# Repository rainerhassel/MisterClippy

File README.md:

# MisterClippy

> Clipping Detector Module

## Dependencies

This project uses symbols from the [moPsy-KiCad-resources](https://github.com/moPsy-project/moPsy-KiCad-resources).

## License

This work is licensed under a [Creative Commons Attribution-ShareAlike 4.0 International License](http://creativecommons.org/licenses/by-sa/4.0/).

BY: Patrick Pickel (@rainerhassel) and Stefan Haun (@penguineer)

See [LICENSE.txt](LICENSE.txt) for details.

Using [moPsy-KiCad-resources](https://github.com/moPsy-project/moPsy-KiCad-resources) by Stefan Haun (mail@tuxathome.de).

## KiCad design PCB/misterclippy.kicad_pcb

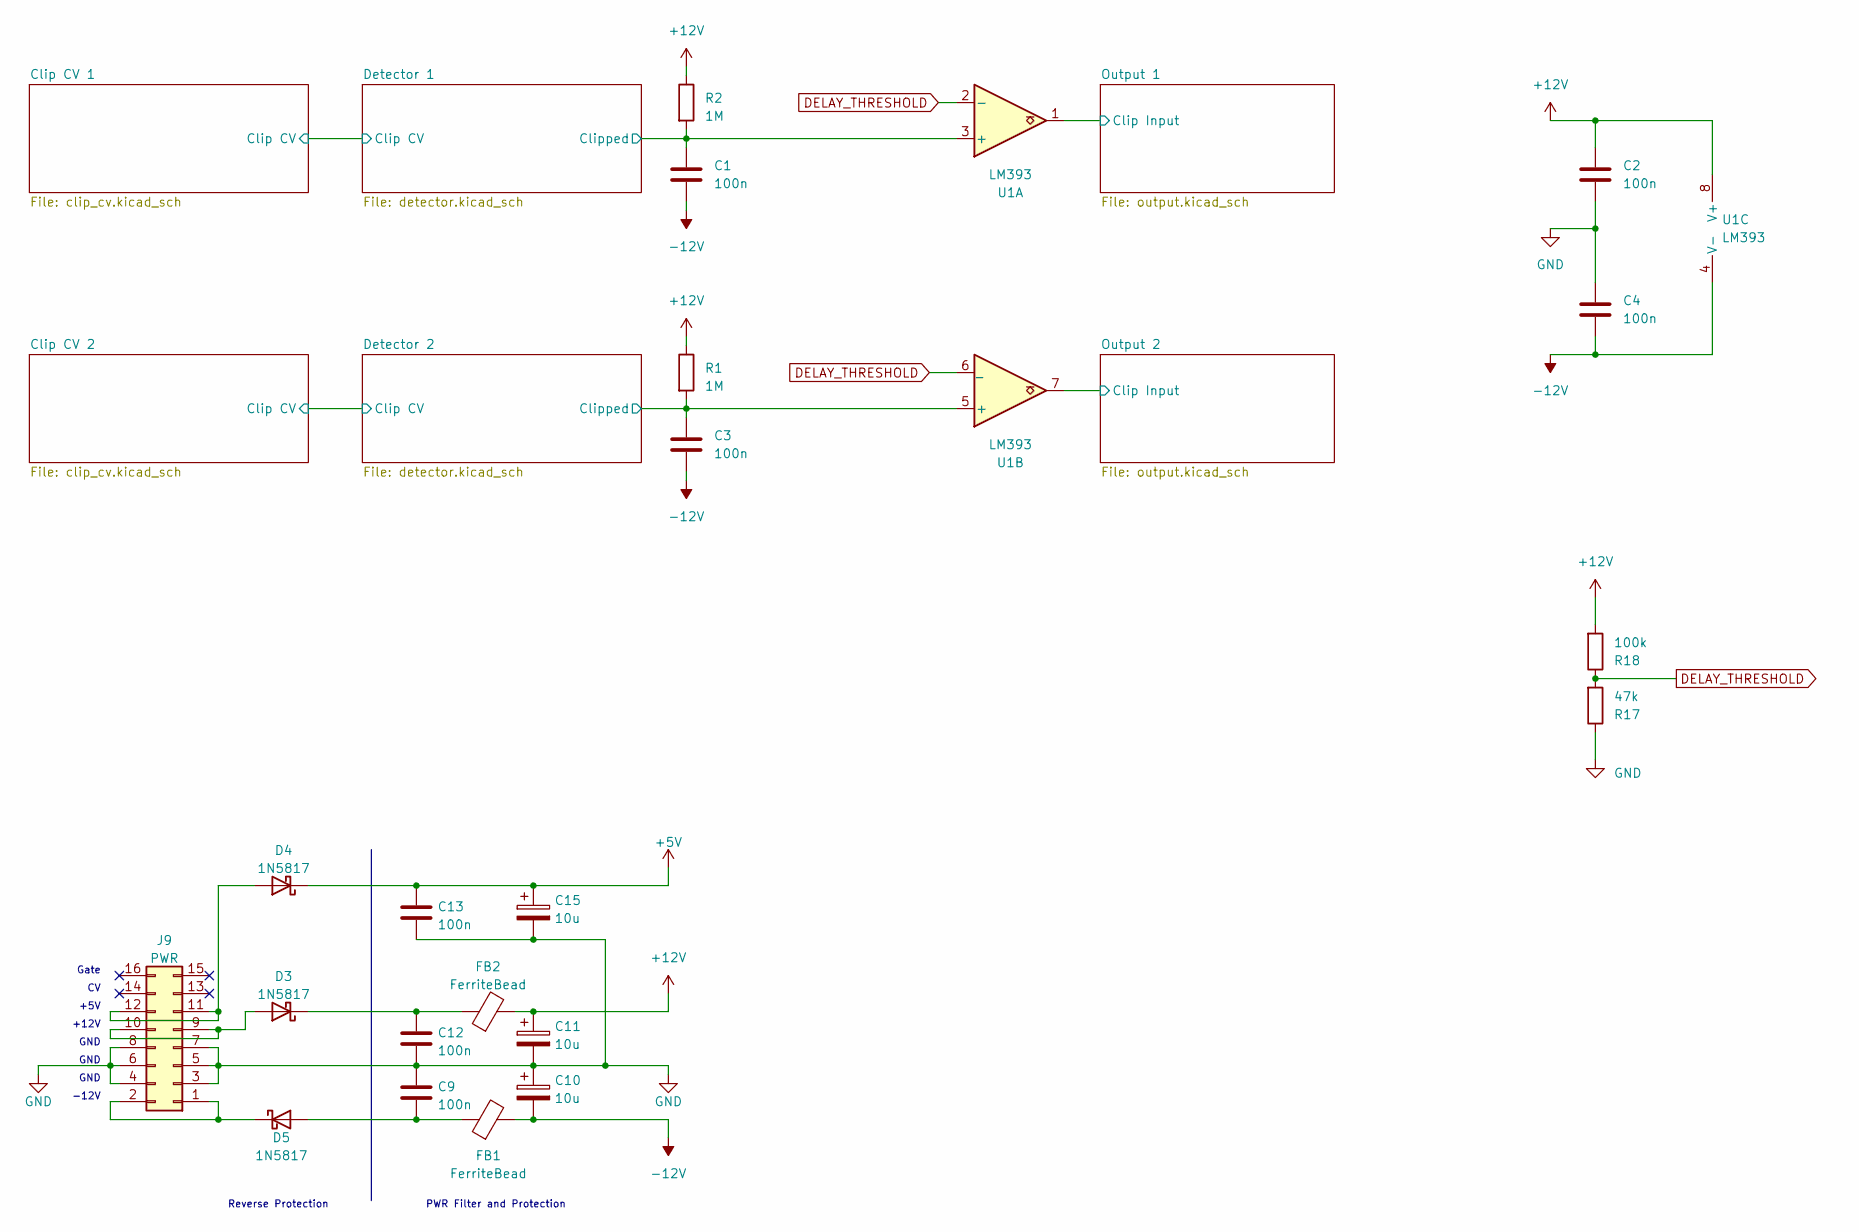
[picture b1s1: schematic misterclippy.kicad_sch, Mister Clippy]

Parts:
C1, C2, C3, C4, C9, C12, C13: 100n; C_Disc_D4.3mm_W1.9mm_P5.00mm
C10, C11, C15: 10u; CP_Radial_D4.0mm_P1.50mm
D3, D4, D5: 1N5817; D_DO-41_SOD81_P7.62mm_Horizontal
FB1, FB2: FerriteBead; FBeadL4D4
J9: PWR; PinHeader_2x08_P2.54mm_Vertical
R1, R2: 1M; R_Axial_DIN0207_L6.3mm_D2.5mm_P7.62mm_Horizontal
R17: 47k; R_Axial_DIN0207_L6.3mm_D2.5mm_P7.62mm_Horizontal
R18: 100k; R_Axial_DIN0207_L6.3mm_D2.5mm_P7.62mm_Horizontal
U1: LM393; DIP-8_W7.62mm

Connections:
+5V: C13.1, C15.1, D4.1 (K); also elsewhere on the board
+12V: C2.1, C11.1, FB2.2, R1.1, R2.1, R18.2, U1.8 (V+); also elsewhere on the board
-12V: C1.2, C3.2, C4.2, C10.2, FB1.2, U1.4 (V-); also elsewhere on the board
/Detector 1/Clipped: C1.1, R2.2, U1.3 (+); also elsewhere on the board
/Detector 2/Clipped: C3.1, R1.2, U1.5 (+); also elsewhere on the board
/Output 1/Clip Input: U1.1; also elsewhere on the board
/Output 2/Clip Input: U1.7; also elsewhere on the board
DELAY_THRESHOLD: R17.2, R18.1, U1.2 (-), U1.6 (_)
GND: C2.2, C4.1, C9.1, C10.1, C11.2, C12.2, C13.2, C15.2, J9.3, J9.4, J9.5, J9.6, J9.7, J9.8, R17.1; also elsewhere on the board
unnamed: D3.2 (A), J9.9, J9.10
unnamed: C12.1, D3.1 (K), FB2.1
unnamed: D4.2 (A), J9.11, J9.12
unnamed: C9.2, D5.2 (A), FB1.1
unnamed: D5.1 (K), J9.1, J9.2

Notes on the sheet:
Gate
GND
+12V
-12V
+5V
Reverse Protection
PWR Filter and Protection

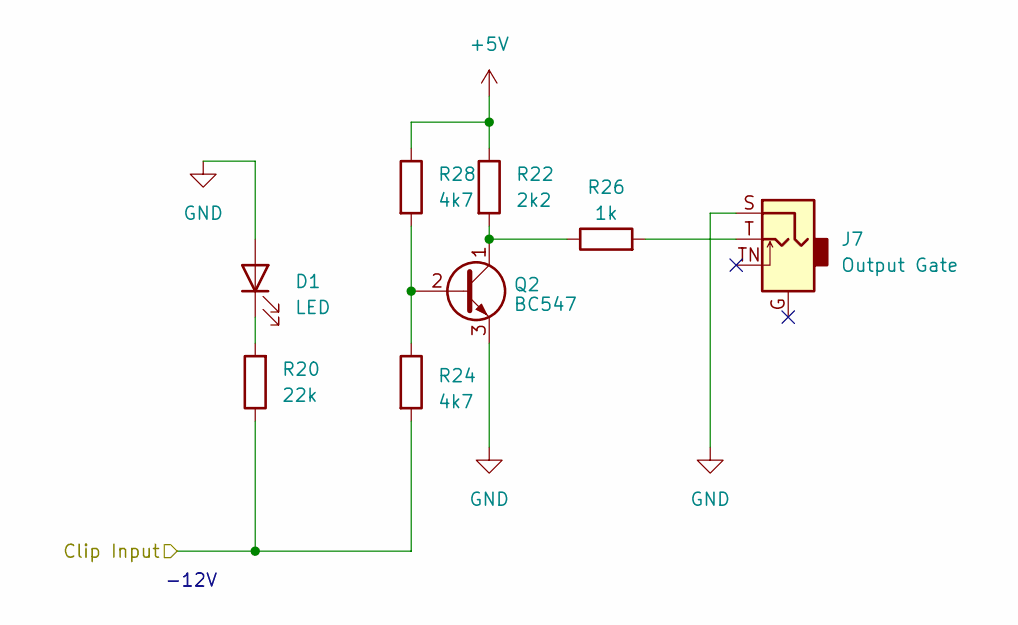
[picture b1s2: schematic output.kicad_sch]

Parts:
D1: LED; LED_D3.0mm
J7: Output Gate; Jack_3.5mm_QingPu_WQP-PJ398SM_Vertical_CircularHoles_Center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
Q2: BC547; TO-92_HandSolder
R20: 22k; R_Axial_DIN0207_L6.3mm_D2.5mm_P7.62mm_Horizontal
R22: 2k2; R_Axial_DIN0207_L6.3mm_D2.5mm_P7.62mm_Horizontal
R24, R28: 4k7; R_Axial_DIN0207_L6.3mm_D2.5mm_P7.62mm_Horizontal
R26: 1k; R_Axial_DIN0207_L6.3mm_D2.5mm_P7.62mm_Horizontal

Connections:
+5V: R22.1, R28.1; also elsewhere on the board
/Output 1/Clip Input: R20.1, R24.2; also elsewhere on the board
GND: D1.2 (A), J7.S, Q2.3 (E); also elsewhere on the board
unnamed: D1.1 (K), R20.2
unnamed: J7.T, R26.2
unnamed: Q2.2 (B), R24.1, R28.2
unnamed: Q2.1 (C), R22.2, R26.1

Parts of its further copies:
D2: LED; LED_D3.0mm
J8: Output Gate; Jack_3.5mm_QingPu_WQP-PJ398SM_Vertical_CircularHoles_Center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
Q1: BC547; TO-92_HandSolder
R19: 22k; R_Axial_DIN0207_L6.3mm_D2.5mm_P7.62mm_Horizontal
R21: 2k2; R_Axial_DIN0207_L6.3mm_D2.5mm_P7.62mm_Horizontal
R23, R27: 4k7; R_Axial_DIN0207_L6.3mm_D2.5mm_P7.62mm_Horizontal
R25: 1k; R_Axial_DIN0207_L6.3mm_D2.5mm_P7.62mm_Horizontal

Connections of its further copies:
+5V: R21.1, R27.1; also elsewhere on the board
/Output 2/Clip Input: R19.1, R23.2; also elsewhere on the board
GND: D2.2 (A), J8.S, Q1.3 (E); also elsewhere on the board
unnamed: D2.1 (K), R19.2
unnamed: J8.T, R25.2
unnamed: Q1.2 (B), R23.1, R27.2
unnamed: Q1.1 (C), R21.2, R25.1

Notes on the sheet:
-12V

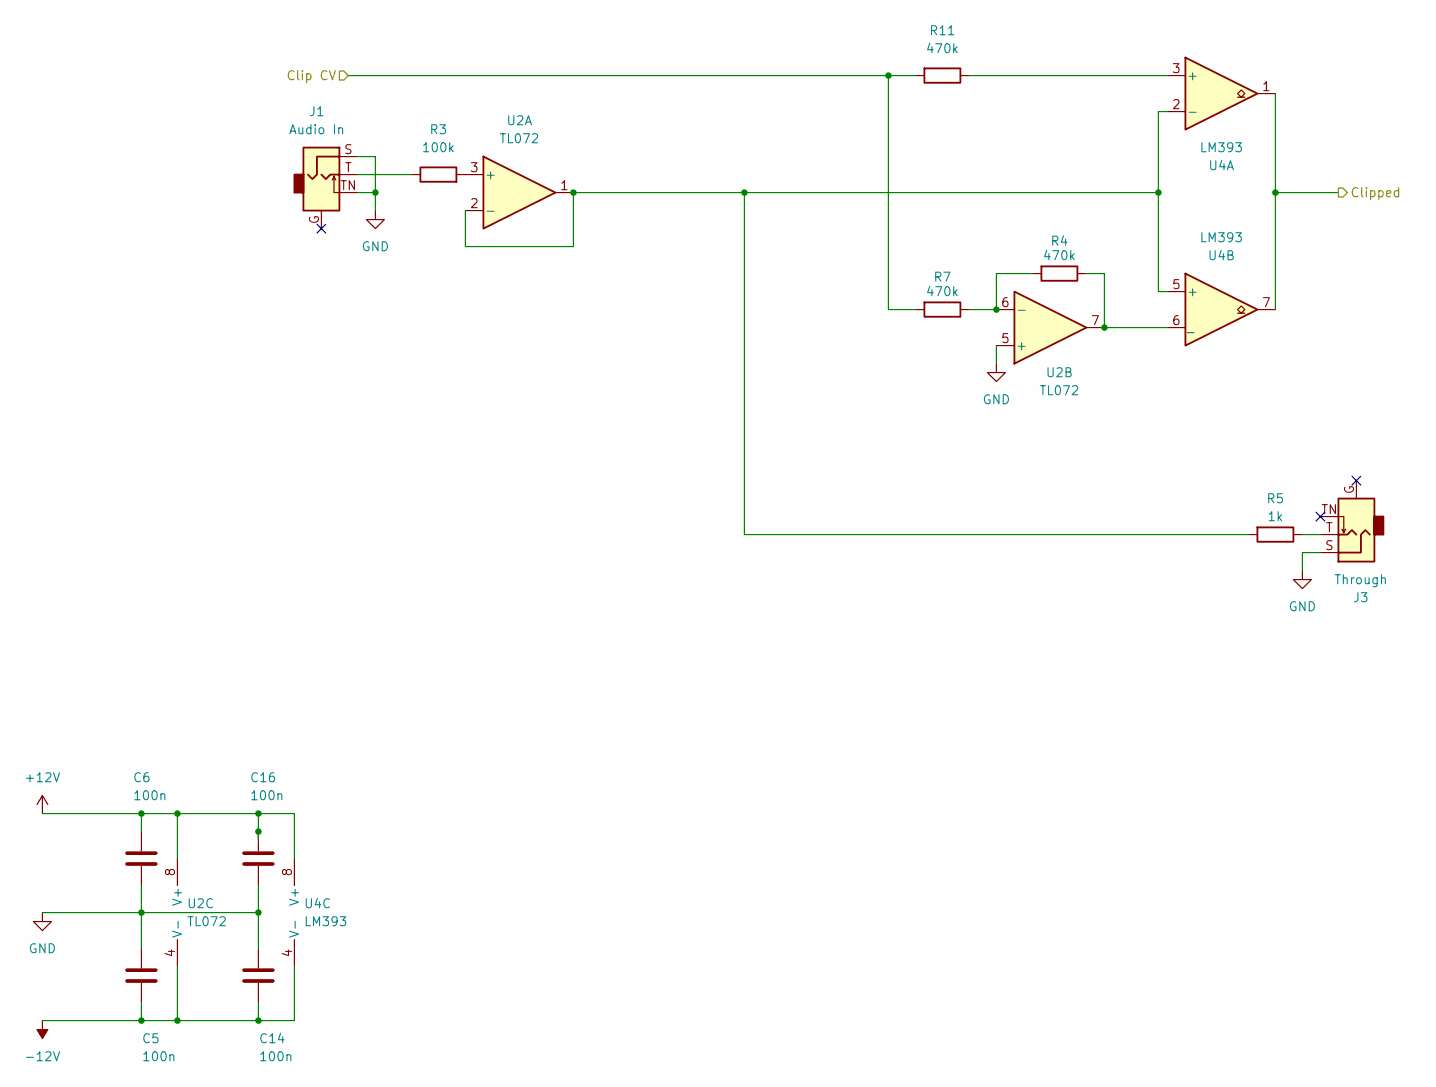
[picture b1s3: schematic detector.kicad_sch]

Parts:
C5, C6, C14, C16: 100n; C_Disc_D4.3mm_W1.9mm_P5.00mm
J1: Audio In; Jack_3.5mm_QingPu_WQP-PJ398SM_Vertical_CircularHoles_Center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
J3: Through; Jack_3.5mm_QingPu_WQP-PJ398SM_Vertical_CircularHoles_Center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
R3: 100k; R_Axial_DIN0207_L6.3mm_D2.5mm_P7.62mm_Horizontal
R4, R7, R11: 470k; R_Axial_DIN0207_L6.3mm_D2.5mm_P7.62mm_Horizontal
R5: 1k; R_Axial_DIN0207_L6.3mm_D2.5mm_P7.62mm_Horizontal
U2: TL072; DIP-8_W7.62mm
U4: LM393; DIP-8_W7.62mm

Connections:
+12V: C6.1, C16.1, U2.8 (V+), U4.8 (V+); also elsewhere on the board
-12V: C5.2, C14.2, U2.4 (V-), U4.4 (V-); also elsewhere on the board
/Clip CV 1/Clip CV: R7.2, R11.2; also elsewhere on the board
/Detector 1/Clipped: U4.1, U4.7; also elsewhere on the board
GND: C5.1, C6.2, C14.1, C16.2, J1.S, J1.TN, J3.S, U2.5 (+); also elsewhere on the board
unnamed: J1.T, R3.1
unnamed: J3.T, R5.1
unnamed: R3.2, U2.3 (+)
unnamed: R5.2, U2.1, U2.2 (-), U4.2 (-), U4.5 (+)
unnamed: R4.2, R7.1, U2.6 (-)
unnamed: R11.1, U4.3 (+)
unnamed: R4.1, U2.7, U4.6 (_)

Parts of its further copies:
C7, C8, C17, C18: 100n; C_Disc_D4.3mm_W1.9mm_P5.00mm
J2: Audio In; Jack_3.5mm_QingPu_WQP-PJ398SM_Vertical_CircularHoles_Center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
J4: Through; Jack_3.5mm_QingPu_WQP-PJ398SM_Vertical_CircularHoles_Center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
R6: 100k; R_Axial_DIN0207_L6.3mm_D2.5mm_P7.62mm_Horizontal
R8: 1k; R_Axial_DIN0207_L6.3mm_D2.5mm_P7.62mm_Horizontal
R9, R10, R12: 470k; R_Axial_DIN0207_L6.3mm_D2.5mm_P7.62mm_Horizontal
U3: TL072; DIP-8_W7.62mm
U5: LM393; DIP-8_W7.62mm

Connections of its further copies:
+12V: C7.1, C18.1, U3.8 (V+), U5.8 (V+); also elsewhere on the board
-12V: C8.2, C17.2, U3.4 (V-), U5.4 (V-); also elsewhere on the board
/Clip CV 2/Clip CV: R10.2, R12.2; also elsewhere on the board
/Detector 2/Clipped: U5.1, U5.7; also elsewhere on the board
GND: C7.2, C8.1, C17.1, C18.2, J2.S, J2.TN, J4.S, U3.5 (+); also elsewhere on the board
unnamed: J2.T, R6.1
unnamed: J4.T, R8.1
unnamed: R6.2, U3.3 (+)
unnamed: R8.2, U3.1, U3.2 (-), U5.2 (-), U5.5 (+)
unnamed: R9.2, R10.1, U3.6 (-)
unnamed: R12.1, U5.3 (+)
unnamed: R9.1, U3.7, U5.6 (_)

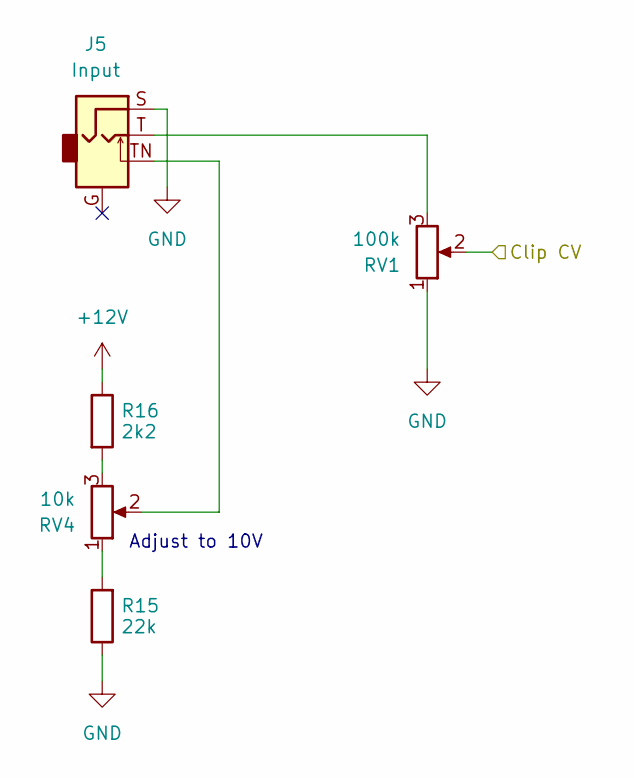
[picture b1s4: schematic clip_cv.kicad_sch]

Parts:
J5: Input; Jack_3.5mm_QingPu_WQP-PJ398SM_Vertical_CircularHoles_Center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
R15: 22k; R_Axial_DIN0207_L6.3mm_D2.5mm_P7.62mm_Horizontal
R16: 2k2; R_Axial_DIN0207_L6.3mm_D2.5mm_P7.62mm_Horizontal
RV1: 100k; Potentiometer_Befaco_12mm_Single_Vertical
RV4: 10k; Potentiometer_Piher_PT-10-V10_Vertical

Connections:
+12V: R16.1; also elsewhere on the board
/Clip CV 1/Clip CV: RV1.2; also elsewhere on the board
GND: J5.S, R15.1, RV1.1; also elsewhere on the board
unnamed: J5.T, RV1.3
unnamed: J5.TN, RV4.2
unnamed: R15.2, RV4.1
unnamed: R16.2, RV4.3

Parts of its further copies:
J6: Input; Jack_3.5mm_QingPu_WQP-PJ398SM_Vertical_CircularHoles_Center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
R13: 22k; R_Axial_DIN0207_L6.3mm_D2.5mm_P7.62mm_Horizontal
R14: 2k2; R_Axial_DIN0207_L6.3mm_D2.5mm_P7.62mm_Horizontal
RV2: 100k; Potentiometer_Befaco_12mm_Single_Vertical
RV3: 10k; Potentiometer_Piher_PT-10-V10_Vertical

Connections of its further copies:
+12V: R14.1; also elsewhere on the board
/Clip CV 2/Clip CV: RV2.2; also elsewhere on the board
GND: J6.S, R13.1, RV2.1; also elsewhere on the board
unnamed: J6.T, RV2.3
unnamed: J6.TN, RV3.2
unnamed: R13.2, RV3.1
unnamed: R14.2, RV3.3

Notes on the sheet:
Adjust to 10V

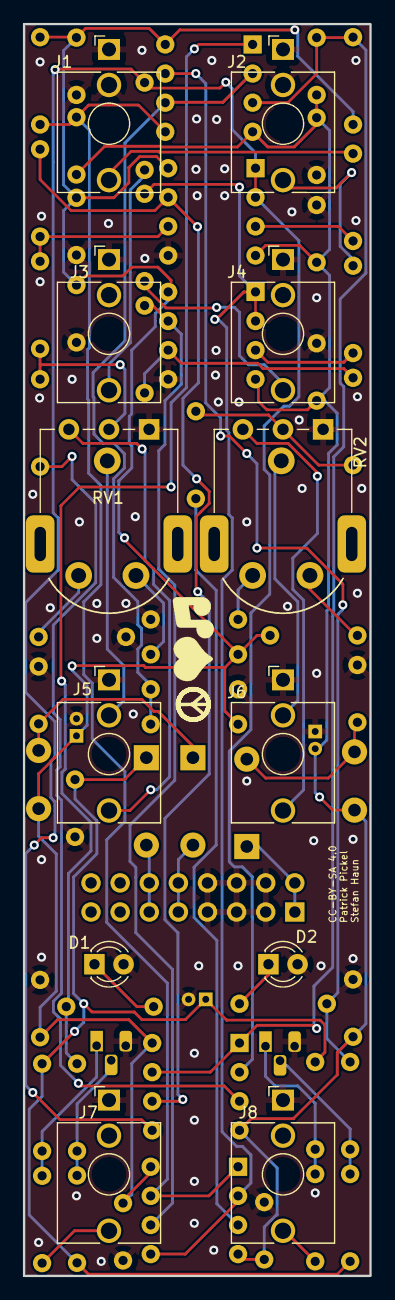
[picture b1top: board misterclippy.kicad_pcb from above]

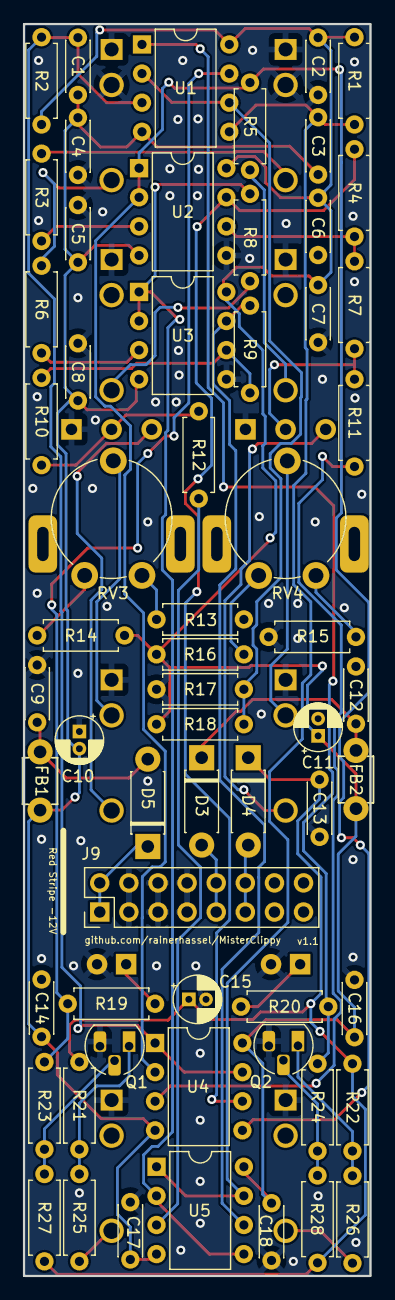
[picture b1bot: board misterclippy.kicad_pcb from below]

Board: 2 copper layers, 30.2 x 109.2 mm, 73 parts (61 on the bottom side), 46 nets.

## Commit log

2023-03-12 add .gitignore for kicad
2023-03-12 initial schematic commit
2023-03-12 :art: Improve layout/positioning on main sheet
    Also condense the voltage divider for the clip delay threshold,
    as there is no load on this part and it can be shared between buffers.
2023-03-12 :art: Adjust layout of Clip CV input
2023-03-12 :bug: Rearrange detector and replace global label
    Global labels in hierarchical sheets lead to connected traces, as the
    label will be connected by name globally.
    Replaced the global label in "Detector" by a wire.
2023-03-12 :wrench: Re-assign component designators
2023-03-12 :wrench: Replace audio jack footprints by centered versions
2023-03-12 PCB layout ready for production
2023-03-12 :memo: Add "Red Stripe" marker on the board
2023-03-13 :art: Try for a design where ICs do not cover jacks
2023-03-13 :art: Turn poti direction around
    Make sure that turning the poti clockwise increases the setting.
2023-03-13 :hammer: Adapt PCB to fixed poti directions
2023-03-15 add panel outline.dxf
2023-04-04 :pencil2: Replace Befaco 12mm poti footprint with fixed verion
    Use footprint based on https://github.com/moPsy-project/moPsy-KiCad-resources/pull/14
    and adjust traces accordingly
2023-05-18 fix schematics after further testing
2023-05-18 Adapt PCB to fixed schematic
2023-05-18 Bump PCB revision number to v1.1
2023-05-18 Add panel graphics as SVG
2023-05-18 Add gitignore for KiCAD project
2023-05-18 Add frontpanel PCB
2023-05-19 :sparkles: Add text "Make Clipping Gate Again" to panel
    Idea by Patrick! :)
2023-05-20 :art: Apply geographical reannotation
2023-05-20 :art: Change transistor footprint for hand soldering
2023-06-05 :art: Adjust voltage divider for Clip CV tap
    Adjust the voltage divider so that 10V are within a good
    adjustment range.
2023-06-05 :wrench: Update resistor value in PCB
2023-06-07 :wrench: Adjust the voltage dividers for Clip CV
2023-06-07 :wrench: Transfer new resistor values to PCB
2023-06-25 :bento: Add moPsy graphic assets
2023-06-26 :bento: Add case shot picture
2023-06-26 :bento: Add figure for calibration
2023-06-26 :bento: Add figure for the frontpanel
2023-06-26 :memo: Add the MisterClippy User Manual tex
2023-06-28 :bento: Add MisterClippy case shot
2023-06-28 :memo: Add case shot picture to README
2023-07-02 :pencil2: Fix name on CC label

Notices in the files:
PCB/misterclippy.kicad_pcb:
CC-BY-SA 4.0
